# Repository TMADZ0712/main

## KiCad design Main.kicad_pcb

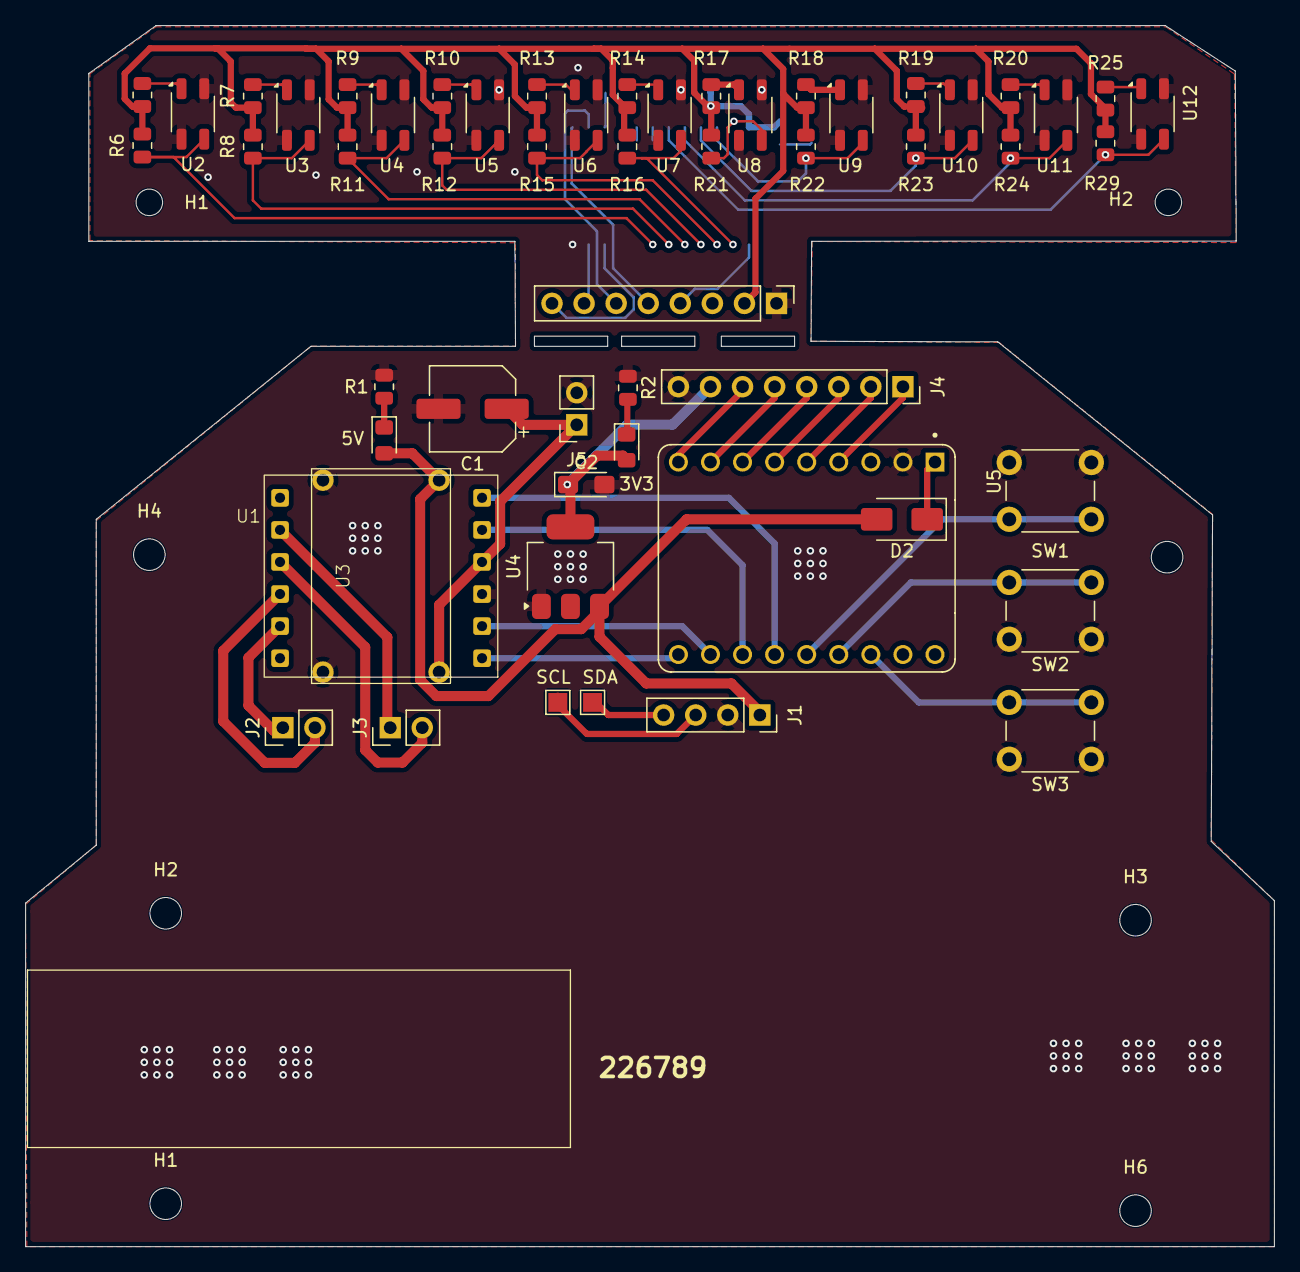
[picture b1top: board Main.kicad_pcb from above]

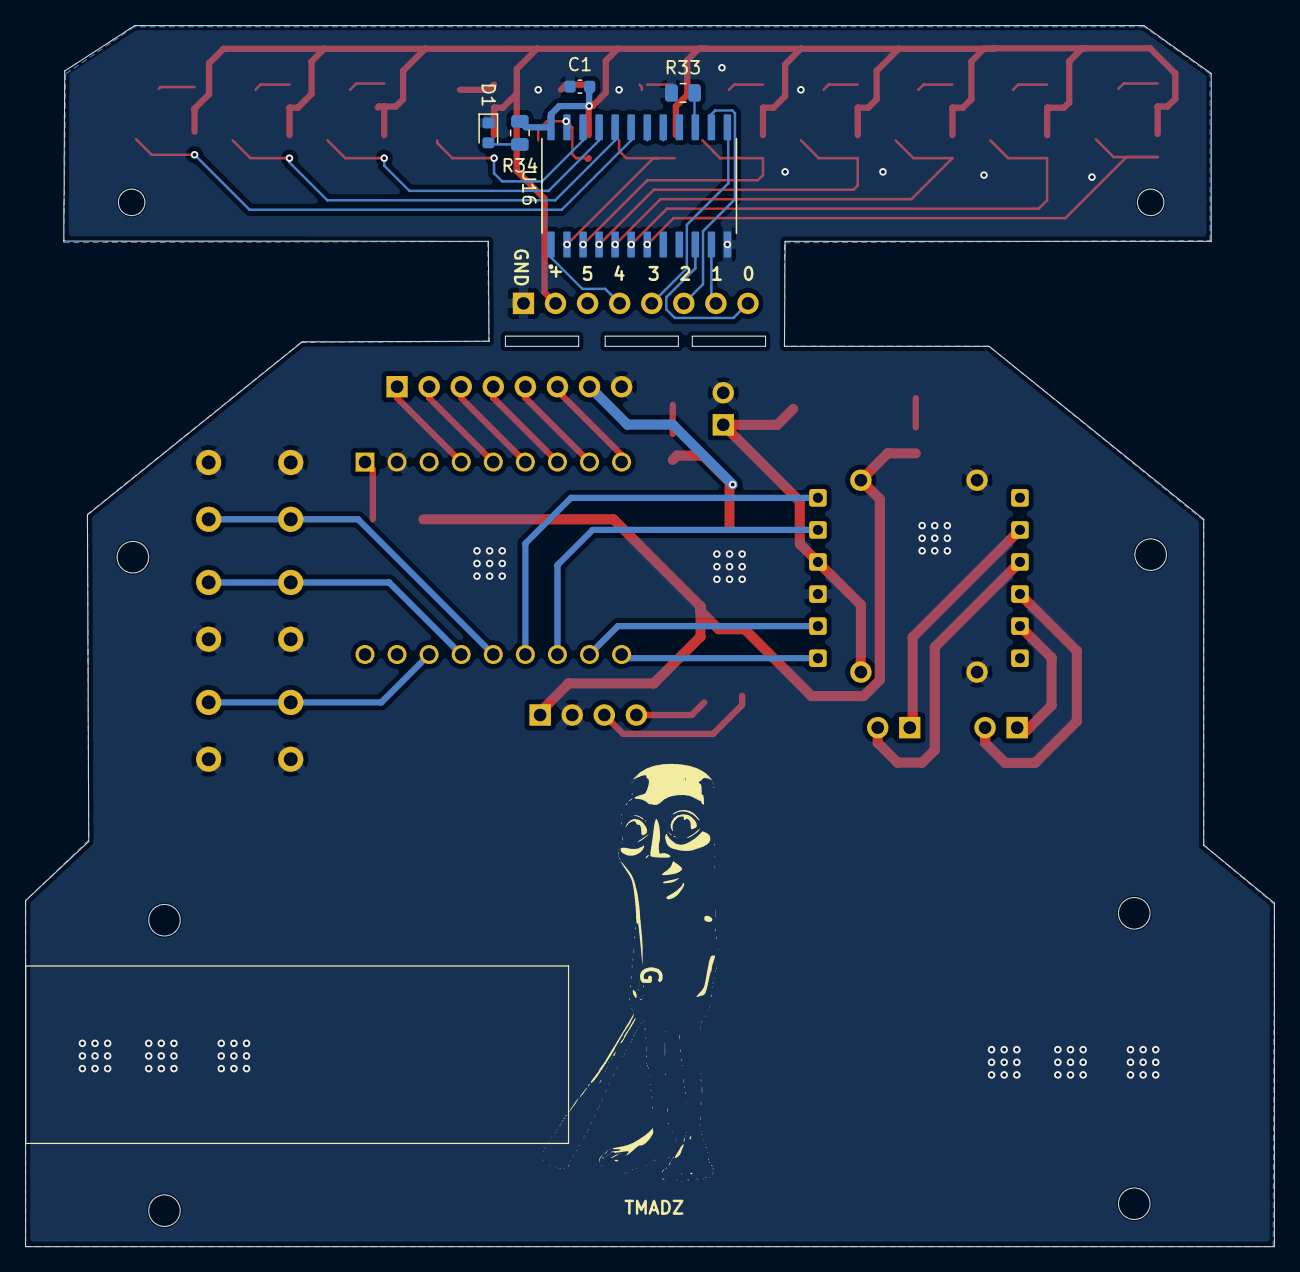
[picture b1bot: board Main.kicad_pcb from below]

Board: 2 copper layers, 98.9 x 96.7 mm, 69 parts (6 on the bottom side), 51 nets.

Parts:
3V3, 5V: LED; LED_0805_2012Metric_Pad1.15x1.40mm_HandSolder
C1: C_Polarized; CP_Elec_6.3x5.8
C1#2: 100uF; C_0603_1608Metric
C2: 10uF; CP_EIA-3216-12_Kemet-S_HandSolder
D1: LED; LED_0603_1608Metric
D2: SS26; D_SMA
G: LOGO
H1, H2, H3, H4, H5, H6: MountingHole_Pad; MountingHole_2.5mm
H1#2, H2#2: MountingHole; MountingHole_2.1mm
J1: Conn_01x06_Pin; PinHeader_1x08_P2.54mm_Vertical
J1#2: Conn_01x04_Socket; PinSocket_1x04_P2.54mm_Vertical
J2, J3: Conn_01x02_Socket; PinHeader_1x02_P2.54mm_Vertical
J4: Conn_01x08_Pin; PinSocket_1x08_P2.54mm_Vertical
J5: Conn_01x02_Socket; PinSocket_1x02_P2.54mm_Vertical
R1, R2, R5, R7, R9, R10, R13, R14, R17, R18, R19, R20, R25: 150; R_0805_2012Metric
R6, R8, R11, R12, R15, R16, R21, R22, R23, R24, R29, R33: 10K; R_0805_2012Metric
R34: 470; R_0805_2012Metric
SCL: TestPoint; TestPoint_Pad_1.5x1.5mm
SDA: TestPoint; TestPoint_Pad_1.5x1.5mm
SW1, SW2, SW3: SW_Push; SW_PUSH_6mm
U1: Untitled
U2, U3#2, U4#2, U5#2, U6, U7, U8, U9, U10, U11, U12: QRE1113GR; OnSemi_CASE100CY
U3: MINI360; Mini360
U4: AMS1117-3.3; SOT-223-3_TabPin2
U5: ESP32-S3-ZERO; MODULE_ESP32-S3-ZERO
U16: CD74HC4067M; SOIC127P1030X265-24N

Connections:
+3.3V: C1#2.1, J1.2, R5.1, R6.1, R7.1, R8.1, R9.1, R10.1, R11.1, R12.1, R13.1, R14.1, R15.1, R16.1, R17.1, R18.1, R19.1, R20.1, R21.1, R22.1, R23.1, R24.1, R25.1, R29.1, R34.2, U16.24 (VCC)
+3V3: 3V3.2 (A), C2.1, J4.7, U4.2 (VO)
+5V: 5V.2 (A), D2.2 (A), J1#2.1, U3.3 (OUT+), U4.3 (VI)
A01: J2.1, U1.8 (AO1)
A02: J2.2, U1.9 (AO2)
AIN1: U1.6 (AIN1), U5.10 (GP10)
AIN2: U1.5 (AIN2), U5.9 (GP9)
B01: J3.1, U1.11 (BO1)
B02: J3.2, U1.10 (BO2)
BIN1: U1.2 (BIN1), U5.8 (GP8)
BIN2: U1.1 (BIN2), U5.7 (GP7)
C2: R6.2, U2.3, U16.7 (I2)
C3: R8.2, U3#2.3, U16.6 (I3)
C4: R11.2, U4#2.3, U16.5 (I4)
C5: R12.2, U5#2.3, U16.4 (I5)
C6: R15.2, U6.3, U16.3 (I6)
C7: R16.2, U7.3, U16.2 (I7)
C8: R21.2, U8.3, U16.23 (I8)
C9: R22.2, U9.3, U16.22 (I9)
C10: R23.2, U10.3, U16.21 (I10)
C11: R24.2, U11.3, U16.20 (I11)
C12: R29.2, U12.3, U16.19 (I12)
GND: C1.2, C1#2.2, C2.2, D1.1 (K), J1.1, J1#2.2, J4.8, J5.2, R1.2, R2.1, R33.1, SW1.1, SW2.1, SW3.1, U1.3 (GND), U2.2 (K), U2.4, U3.2 (IN-), U3.4 (OUT-), U3#2.2 (K), U3#2.4, U4.1 (GND), U4#2.2 (K), U4#2.4, U5.GND, U5#2.2 (K), U5#2.4, U6.2 (K), U6.4, U7.2 (K), U7.4, U8.2 (K), U8.4, U9.2 (K), U9.4, U10.2 (K), U10.4, U11.2 (K), U11.4, U12.2 (K), U12.4, U16.12 (GND)
LS: J4.6, U5.6 (GP6)
unnamed: D1.2 (A), R34.1
unnamed: 5V.1 (K), R1.1
unnamed: D2.1 (K), U5.5V
unnamed: 3V3.1 (K), R2.2
unnamed: R5.2, U2.1 (A)
unnamed: R7.2, U3#2.1 (A)
unnamed: R9.2, U4#2.1 (A)
unnamed: R10.2, U5#2.1 (A)
unnamed: R13.2, U6.1 (A)
unnamed: R14.2, U7.1 (A)
unnamed: R17.2, U8.1 (A)
unnamed: R18.2, U9.1 (A)
unnamed: R19.2, U10.1 (A)
unnamed: R20.2, U11.1 (A)
unnamed: R25.2, U12.1 (A)
unnamed: R33.2, U16.15 (~E)
S: J1.4, J4.5, U5.5 (GP5), U16.1 (COMMON_I/O)
S0: J1.8, J4.1, U5.1 (GP1), U16.10 (S0)
S1: J1.7, J4.2, U5.2 (GP2), U16.11 (S1)
S2: J1.6, J4.3, U5.3 (GP3), U16.14 (S2)
S3: J1.5, J4.4, U5.4 (GP4), U16.13 (S3)
SCL: J1#2.3, SCL.1 (1_1)
SDA: J1#2.4, SDA.1 (1_1)
SW1: SW1.2, U5.11 (GP11)
SW2: SW2.2, U5.12 (GP12)
SW3: SW3.2, U5.13 (GP13)
VCC: C1.1, J5.1, U1.4 (VCC), U3.1 (IN+)
